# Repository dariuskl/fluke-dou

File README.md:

# Data Output Units for Vintage Fluke Meters

This is a collection of firmware and PCBs mean to be used in vintage Fluke
meters such as the 8000A, 1900A, etc. They provide the measurements of the
meter on a USB serial port and might also provide other features such as
the possibility to power the meter via that USB port.

The firmware targets the MSP430G2xx series of microcontrollers despite them
being neither vintage nor 5 V devices. They were chosen due to their good
availability, ease-of-use, good compiler support, wide range of package
options (including DIP), and affordability. (Most modern 5V parts just have
internal regulators anyway, due to modern lithography, so we' just be saving
us the level shifting, but some devices require more than a level shifter
anyway.)

Code is written in C, decode logic and platform-specific stuff is separated
as much as possible. So porting this to a different controller should be
straight-forward. The build is run by `make` as a jumbo build.

## 1900A — Multi-Counter

- PCB is already designed
- C++ code exists, also ported here, but not yet tested

See https://github.com/dariuskl/fluke_1900a_usb_dou

## 8000A — Digital Multimeter

**Firmware** — first working version available with tag `8000a-fw-1`
**Hardware** — PCB not yet designed, working on perfboard prototype

The 8000A is a very early multimeter with limited data output capabilities. It
offers only signals for the digits, none for the decimal point or range and
mode information.

The serial output is default configured to 19200 baud 7N1 and transmits the
readings as outlined below.

    <overload><polarity><MSD><2SD><3SD><LSD>\r\n

### Modifications Required for Battery Pack (Option -01)

The battery pack PCB does not have routing for all signals required by the DOU
onto the finger connector. The two-layered board just could not accommodate
both the traces required for the batteries and the DOU. This can be fixed with
a few jumper wires, though.

**TODO: insert a schema showing what points to connect here**

### Finger Connector Pinout

The finger conector is a card edge connector at the back of the main PCB. It
is double-sides, i.e. there might be different signals on the top and bottom
side of the board. Most handily, the Fluke engineers put some pracitcal vias
with a 2.54 mm pitch through ten of those connections, plus one extra via to
the side, but perfectly in grid. This is where a 11-position pin receptable
will find its place.

The signal `nT` is actually not part of the finger connector, but it does have
a strategically placed via. As it is next to pin 1 of the finger connector, I
assigned it the pin number zero.

Not all signals have suitable logic levels to interface to a 5 V µC (let alone
the 3.3 V MSP430), so comparators are used to condition the signals according
to the thresholds that I determined for each signal.

(Note that the given high and low voltage levels are ballpark figures.)

| Pin | Signal | Description        | Low level | High level  | Threshold |
|-----|--------|--------------------|-----------|-------------|-----------|
| 0   | nT     | Measurement period | 1.2 V     | 4.8 V       | 2.5 V     |
| 2   | nZERO  | ???                |           |             |           |
| 4   | S1     | MSD strobe         | 0 V       | 4.6 V       | 2.5 V     |
| 6   | S4     | LSD strobe         | 0 V       | 3.3 V       | 1.6 V     |
| 8   | S      | Strobe clock       | 0 V       | 2.5...4.6 V | 1.6 V     |
| 10  | +5V    | Regulated 5V rail  | —         | —           | —         |
| 12  | GND    | Ground             | —         | —           | —         |
| 14  | Y      | BCD 4              | 0 V       | 4.9 V       | 2.5 V     |
| 16  | X      | BCD 2              | 0 V       | 4.9 V       | 2.5 V     |
| 18  | W      | BCD 8              | 0 V       | 4.9 V       | 2.5 V     |
| 20  | Z      | BCD 1              | 0 V       | 4.9 V       | 2.5 V     |

### Protocol

| Digit     | W        | X     | Y        | Z     | Strobe |
|-----------|----------|-------|----------|-------|--------|
| DS1 (MSD) | overload | ?     | polarity | MSD   | S1     |
| DS2..DS3  | BCD 8    | BCD 4 | BCD 2    | BCD 1 | none   |
| DS4 (LSD) | BCD 8    | BCD 4 | BCD 2    | BCD 1 | S4     |

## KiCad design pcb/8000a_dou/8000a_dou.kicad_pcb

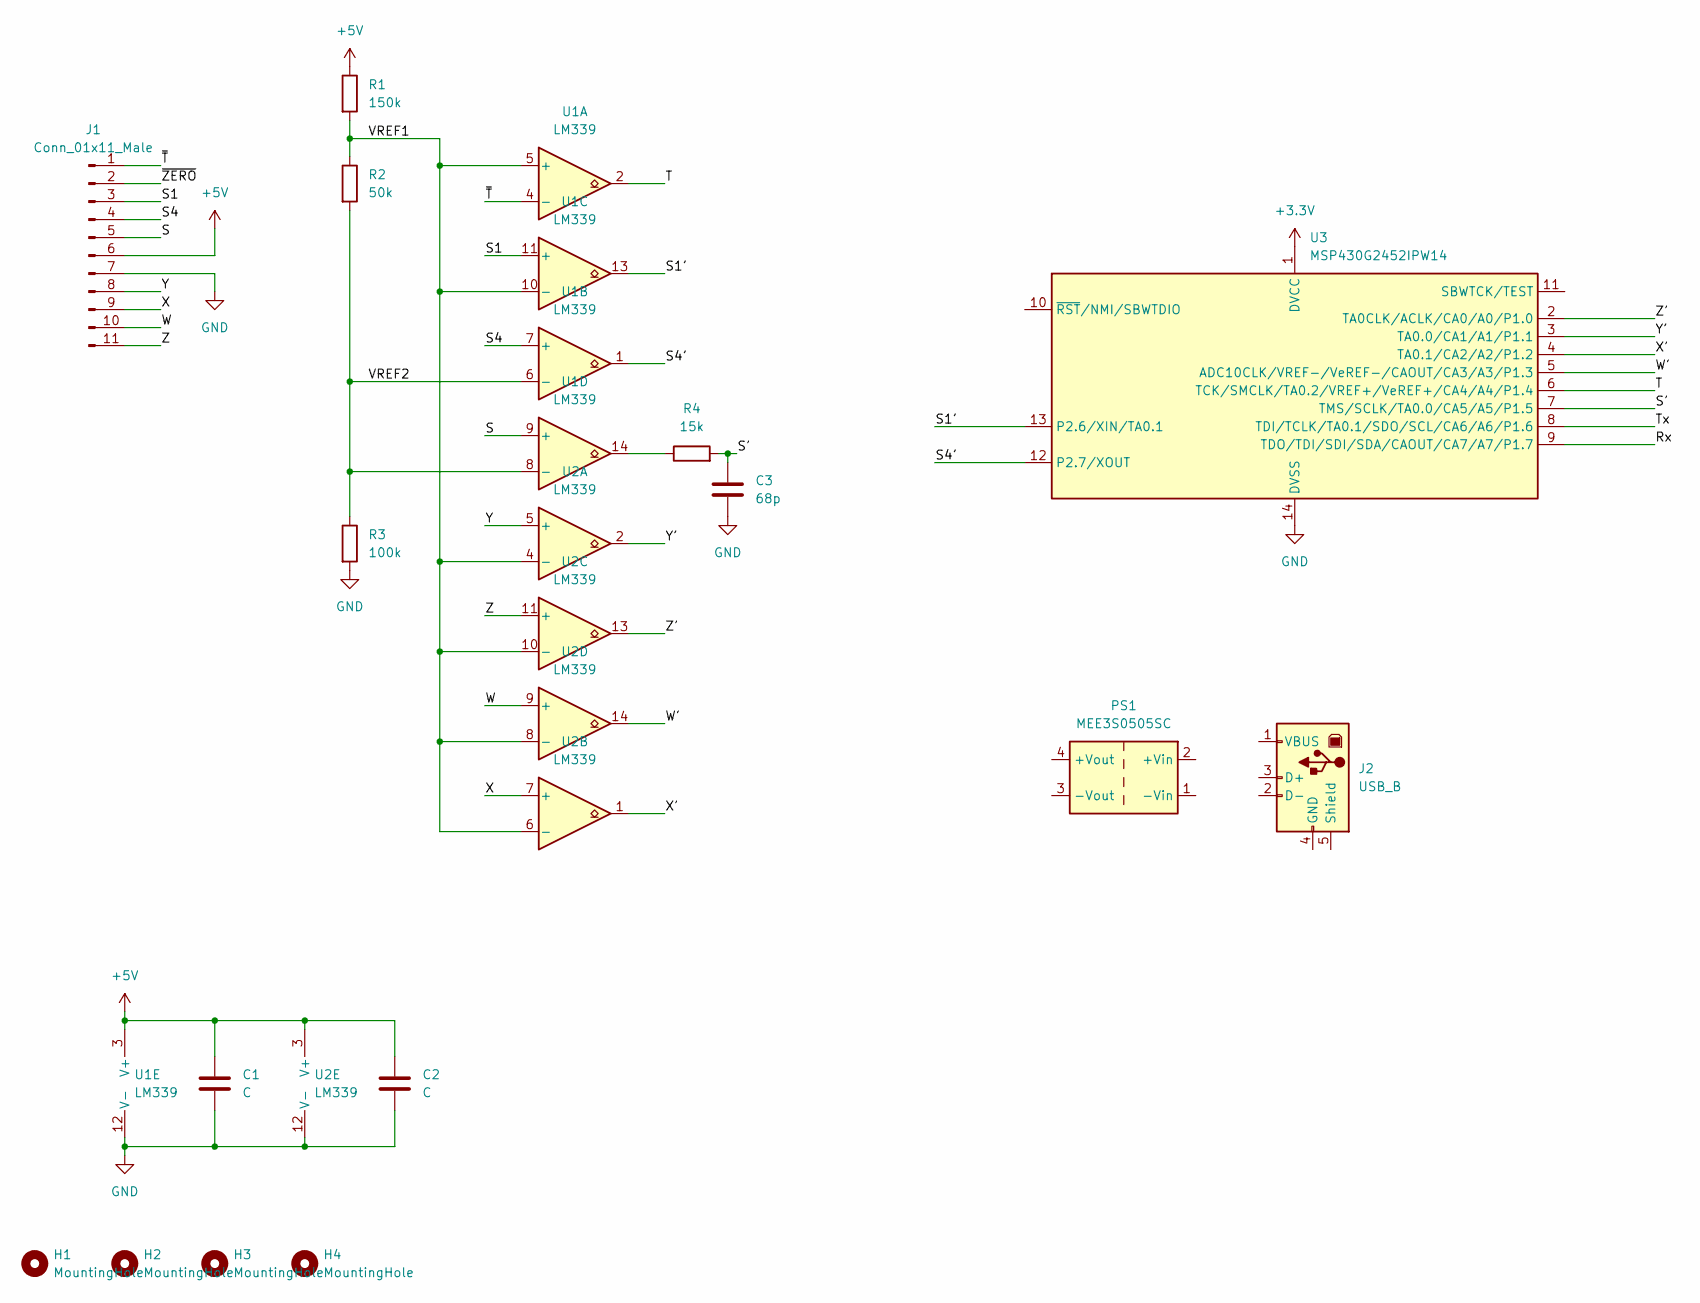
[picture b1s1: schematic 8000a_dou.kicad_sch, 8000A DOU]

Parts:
C1, C2: C; C_0805_2012Metric
C3: 68p; C_0805_2012Metric
H1, H2, H3, H4: MountingHole; MountingHole_3.2mm_M3
J1: Conn_01x11_Male; PinHeader_1x11_P2.54mm_Vertical
J2: USB_B; USB_B_Lumberg_2411_02_Horizontal
PS1: MEE3S0505SC; Converter_DCDC_Murata_MEE3SxxxxSC_THT
R1: 150k; R_Axial_DIN0207_L6.3mm_D2.5mm_P10.16mm_Horizontal
R2: 50k; R_Axial_DIN0207_L6.3mm_D2.5mm_P10.16mm_Horizontal
R3: 100k; R_Axial_DIN0207_L6.3mm_D2.5mm_P10.16mm_Horizontal
R4: 15k; R_Axial_DIN0207_L6.3mm_D2.5mm_P10.16mm_Horizontal
U1, U2: LM339; SOIC-14_3.9x8.7mm_P1.27mm
U3: MSP430G2452IPW14; TSSOP-14_4.4x5mm_P0.65mm

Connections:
+3V3: U3.1 (DVCC)
+5V: C1.1, C2.1, J1.6, R1.1, U1.3 (V+), U2.3 (V+)
/Rx: U3.9 (TDO/TDI/SDI/SDA/CAOUT/CA7/A7/P1.7)
/S: J1.5, U1.9 (+)
/S1: J1.3, U1.11 (+)
/S1': U1.13, U3.13 (P2.6/XIN/TA0.1)
/S4: J1.4, U1.7 (+)
/S4': U1.1, U3.12 (P2.7/XOUT)
/S': C3.1, R4.2, U3.7 (TMS/SCLK/TA0.0/CA5/A5/P1.5)
/T: U1.2, U3.6 (TCK/SMCLK/TA0.2/VREF+/VeREF+/CA4/A4/P1.4)
/Tx: U3.8 (TDI/TCLK/TA0.1/SDO/SCL/CA6/A6/P1.6)
/VREF1: R1.2, R2.1, U1.5 (+), U1.10 (-), U2.4 (-), U2.6 (-), U2.8 (-), U2.10 (-)
/VREF2: R2.2, R3.1, U1.6 (-), U1.8 (-)
/W: J1.10, U2.9 (+)
/W': U2.14, U3.5 (ADC10CLK/VREF-/VeREF-/CAOUT/CA3/A3/P1.3)
/X: J1.9, U2.7 (+)
/X': U2.1, U3.4 (TA0.1/CA2/A2/P1.2)
/Y: J1.8, U2.5 (+)
/Y': U2.2, U3.3 (TA0.0/CA1/A1/P1.1)
/Z: J1.11, U2.11 (+)
/Z': U2.13, U3.2 (TA0CLK/ACLK/CA0/A0/P1.0)
/~T: J1.1, U1.4 (-)
/~ZERO: J1.2
GND: C1.2, C2.2, C3.2, J1.7, R3.2, U1.12 (V-), U2.12 (V-), U3.14 (DVSS)
unnamed: R4.1, U1.14

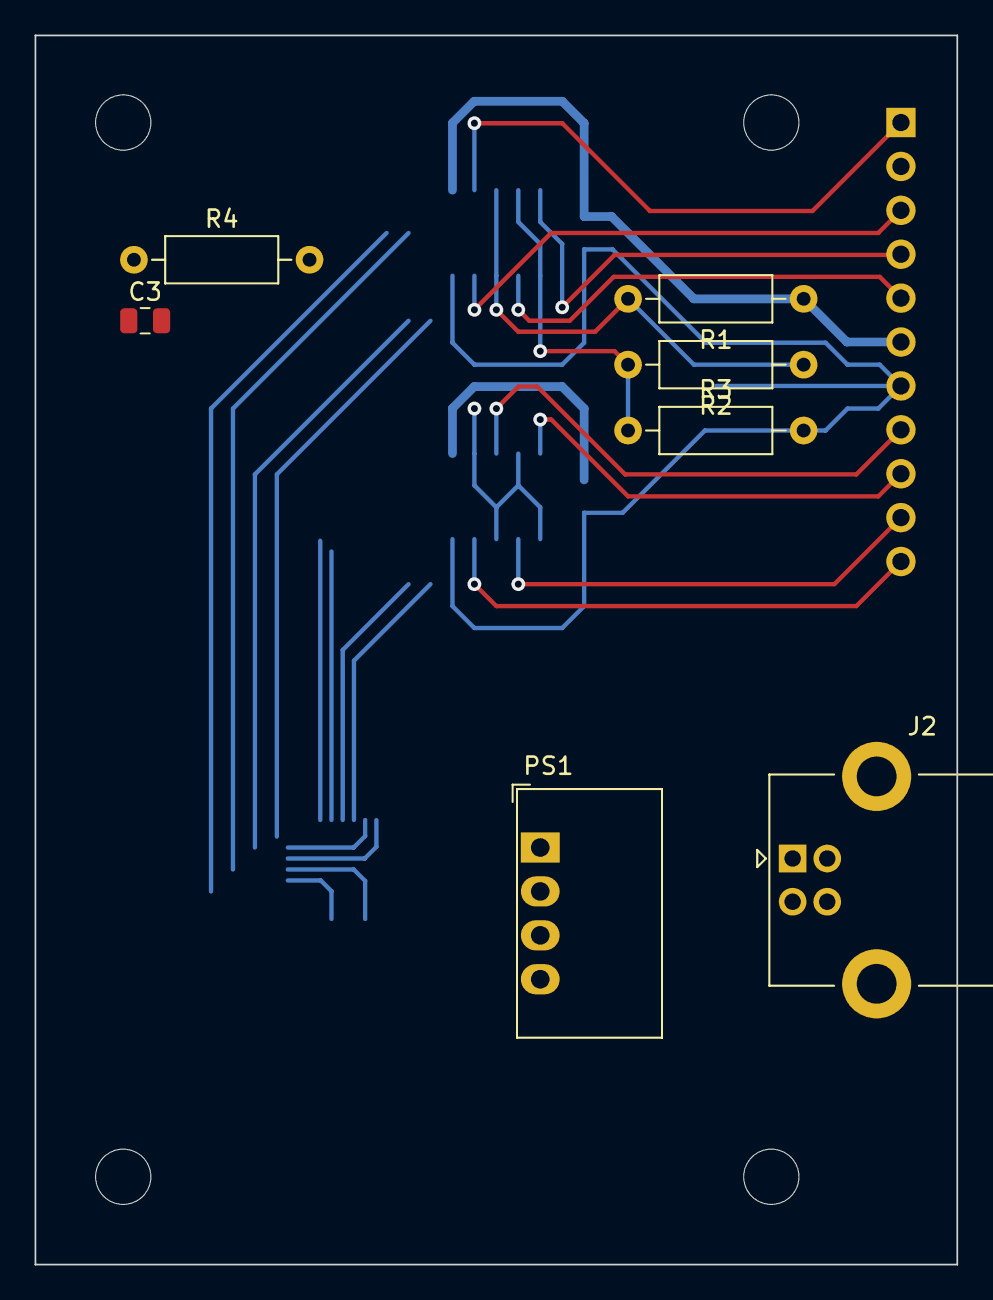
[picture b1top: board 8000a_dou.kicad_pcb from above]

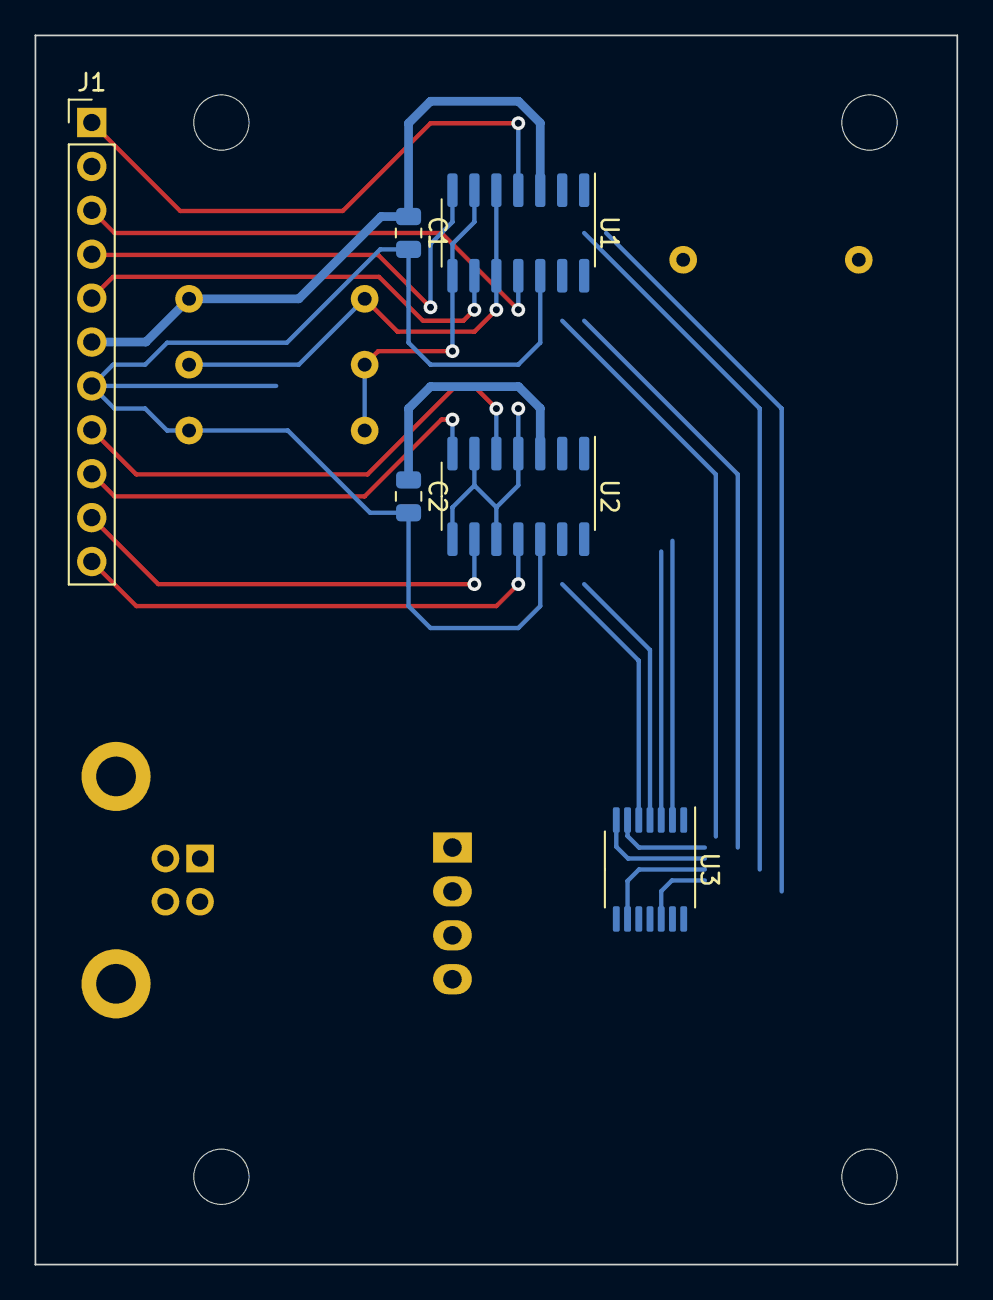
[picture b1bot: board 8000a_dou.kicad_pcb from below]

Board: 2 copper layers, 53.3 x 71.1 mm, 17 parts (6 on the bottom side), 21 nets.

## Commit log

2024-07-16 implement first draft of 8000A firmware
2024-07-18 lots of progress
    - serial via USI works
    - info util helps re-writing device calibration
    - found out that MSPG2231 has no 16MHz factory calibration
2024-07-21 8000A works mostly; logic levels not OK yet
2024-07-21 split decode logic and IO logic
2024-07-21 remove dependencies to standard lib
2024-07-26 debugging the 8000A
2024-07-26 can capture input from 8000A, but ...
    - not every cycle is seeing output on serial
    - readings are consistently output on serial while T is low,
    should be just once
    - watchdog is disabled for now, because it screws up everything
2024-07-27 implement rudimentary tests for 8000A
2024-07-27 more debugging on the 8000A
2024-07-27 put low-pass filter on S'
2024-08-08 rename DOU PCB project
    Perhaps further PCBs for the 8000A will be designed or a reproduction of
    the original schematic.
2024-08-08 software for the 8000A finally works
2024-08-08 move logic out of the fw part ot the fsm
2024-08-09 project description in README & minor Makefile fix
